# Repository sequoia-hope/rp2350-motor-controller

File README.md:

# rp2350-motor-controller

---- work in progress ----

This board is open source.

Design by Sequoia Hope Alexander. 

I want to build tools that help people get what they need. 

Follow me on Bluesky:
    https://bsky.app/profile/sequoia.farm

CERN-OHL-P license. See LICENSE file for details.

A brushless motor controller and servomotor controller for robotics.

This board is designed to be fabricated at JLCPCB by anyone. All of the
components have been sourced to be in stock in high volumes and low cost
at LCSC/JLCPCB. When the board is ready, you can order them yourself at cost
by uploading a zip file to JLCPCB for under $50 per board QTY 10.

Board features:
--
 - Dual core 150MHz RP2350B CPU with floating point and excellent firmware APIs
 - Four independent software-controlled half-h bridges
 - Supports brushless motors, stepper motors, or two brushed motors.
 - SimpleFOC firmware support
 - Maximum 60 volts on 80V silicon (FETs, buck), with TVS breakdown set just
   below the FET rating so surges hit the TVS first (SMAJ64A phases, SMDJ64A
   bus). Rev A boards are limited to ~48V by their 51V-standoff phase TVS.
   A 72V-bus variant needs six BOM changes (100V FETs, 78A-grade TVS, 100V
   buck, 4.3k divider bottoms, no LM74700) — see review/power.html.
 - Current range set by the phase shunts — see the table below
 - Phase voltage sensing for three phases
 - Phase current sensing for three phases
 - Input voltage sensing
 - Temperature sensing for both the FETS and motor.
 - Isolated CAN bus port
 - USB-C can be used for Micropython development, USB serial, or gamepad emulation for force feedback wheels or other devices.
 - Advanced 12-pin encoder port
    - Active signal switching reroutes physical I/O pins to multiple signal conditioning circuits.
    - Four bidirectional differential line drivers with common mode filters
    - Switchable filtering for single ended hall sensor support
    - Support for single ended or differential SPI or quadrature encoders
    - Dual channel analog encoder support for sin/cos or linear analog sensors
    - I2C sensor support
    - Switchable encoder output voltage - 3.3v or 5v - so nearly any sensor can easily be connected
    - Unused line drivers can be used as additional high speed bidirectional comms.
 - All configuration happens in software, no jumpers needed. 
 - Expandable emergency stop circuit

 - Phase and encoder leads on one side of the board, data connectors on the other
    - It is possible to design a PCB which mates to both the phase and encoder leads, to make connector adapter PCBs to your preferred motor and encoder PCBs.
 - Boards can be daisy-chained side to side, passing motor power and data via serial.
 
Current sensing (INA240A1D, 20x gain, mid-rail reference):
--
The measurable range is set by the phase shunt value. Keep the firmware
`SHUNT_RESISTOR` define in sync with what is populated, and keep
`current_limit` below the saturation ceiling (the firmware clamps this).

| Shunt (per phase) | V/A  | Measurable range |
|-------------------|------|------------------|
| 20 mΩ             | 0.40 | ±4.1 A           |
| 10 mΩ             | 0.20 | ±8.2 A           |
| 5 mΩ              | 0.10 | ±16.5 A          |
| 2×8 mΩ (=4 mΩ, schematic default) | 0.08 | ±20.6 A |

Encoder port, single-ended vs differential (rev B):
--
Each channel's 100Ω termination sits behind an analog switch on `TERM_SW`
(GPIO38). Firmware drives it high for differential encoders (termination in
circuit) and low for single-ended ones — with the termination open, the
10k/10k bias holds the unused receiver input at 1.65V and any 3.3V/5V
single-ended signal clears the threshold with >1.5V of margin; 10k pull-ups
on the P lines support open-collector outputs. On rev A boards (fixed
termination) single-ended signals cannot cross the receiver threshold on the
transceiver path: use the hall path (pins 11/9/7) for single-ended
quadrature, or swap the bias resistors R86–R93 to 560Ω for push-pull
single-ended signals. GPIO38 reaches test point TP20 on rev A for bodges.
Additionally:
 ---
 - No special programmer is required, no bootloader needs to be flashed.
 - Supports the Raspberry Pi debugger board, or use the compatible custom debugger board which can be fabbed at JLCPCB as well.
    - https://github.com/sequoia-hope/rp2040-motor-controller/tree/main/debugger
 - PlatformIO and VSCode support with step debugging, breakpoints, memory and register views.

-------

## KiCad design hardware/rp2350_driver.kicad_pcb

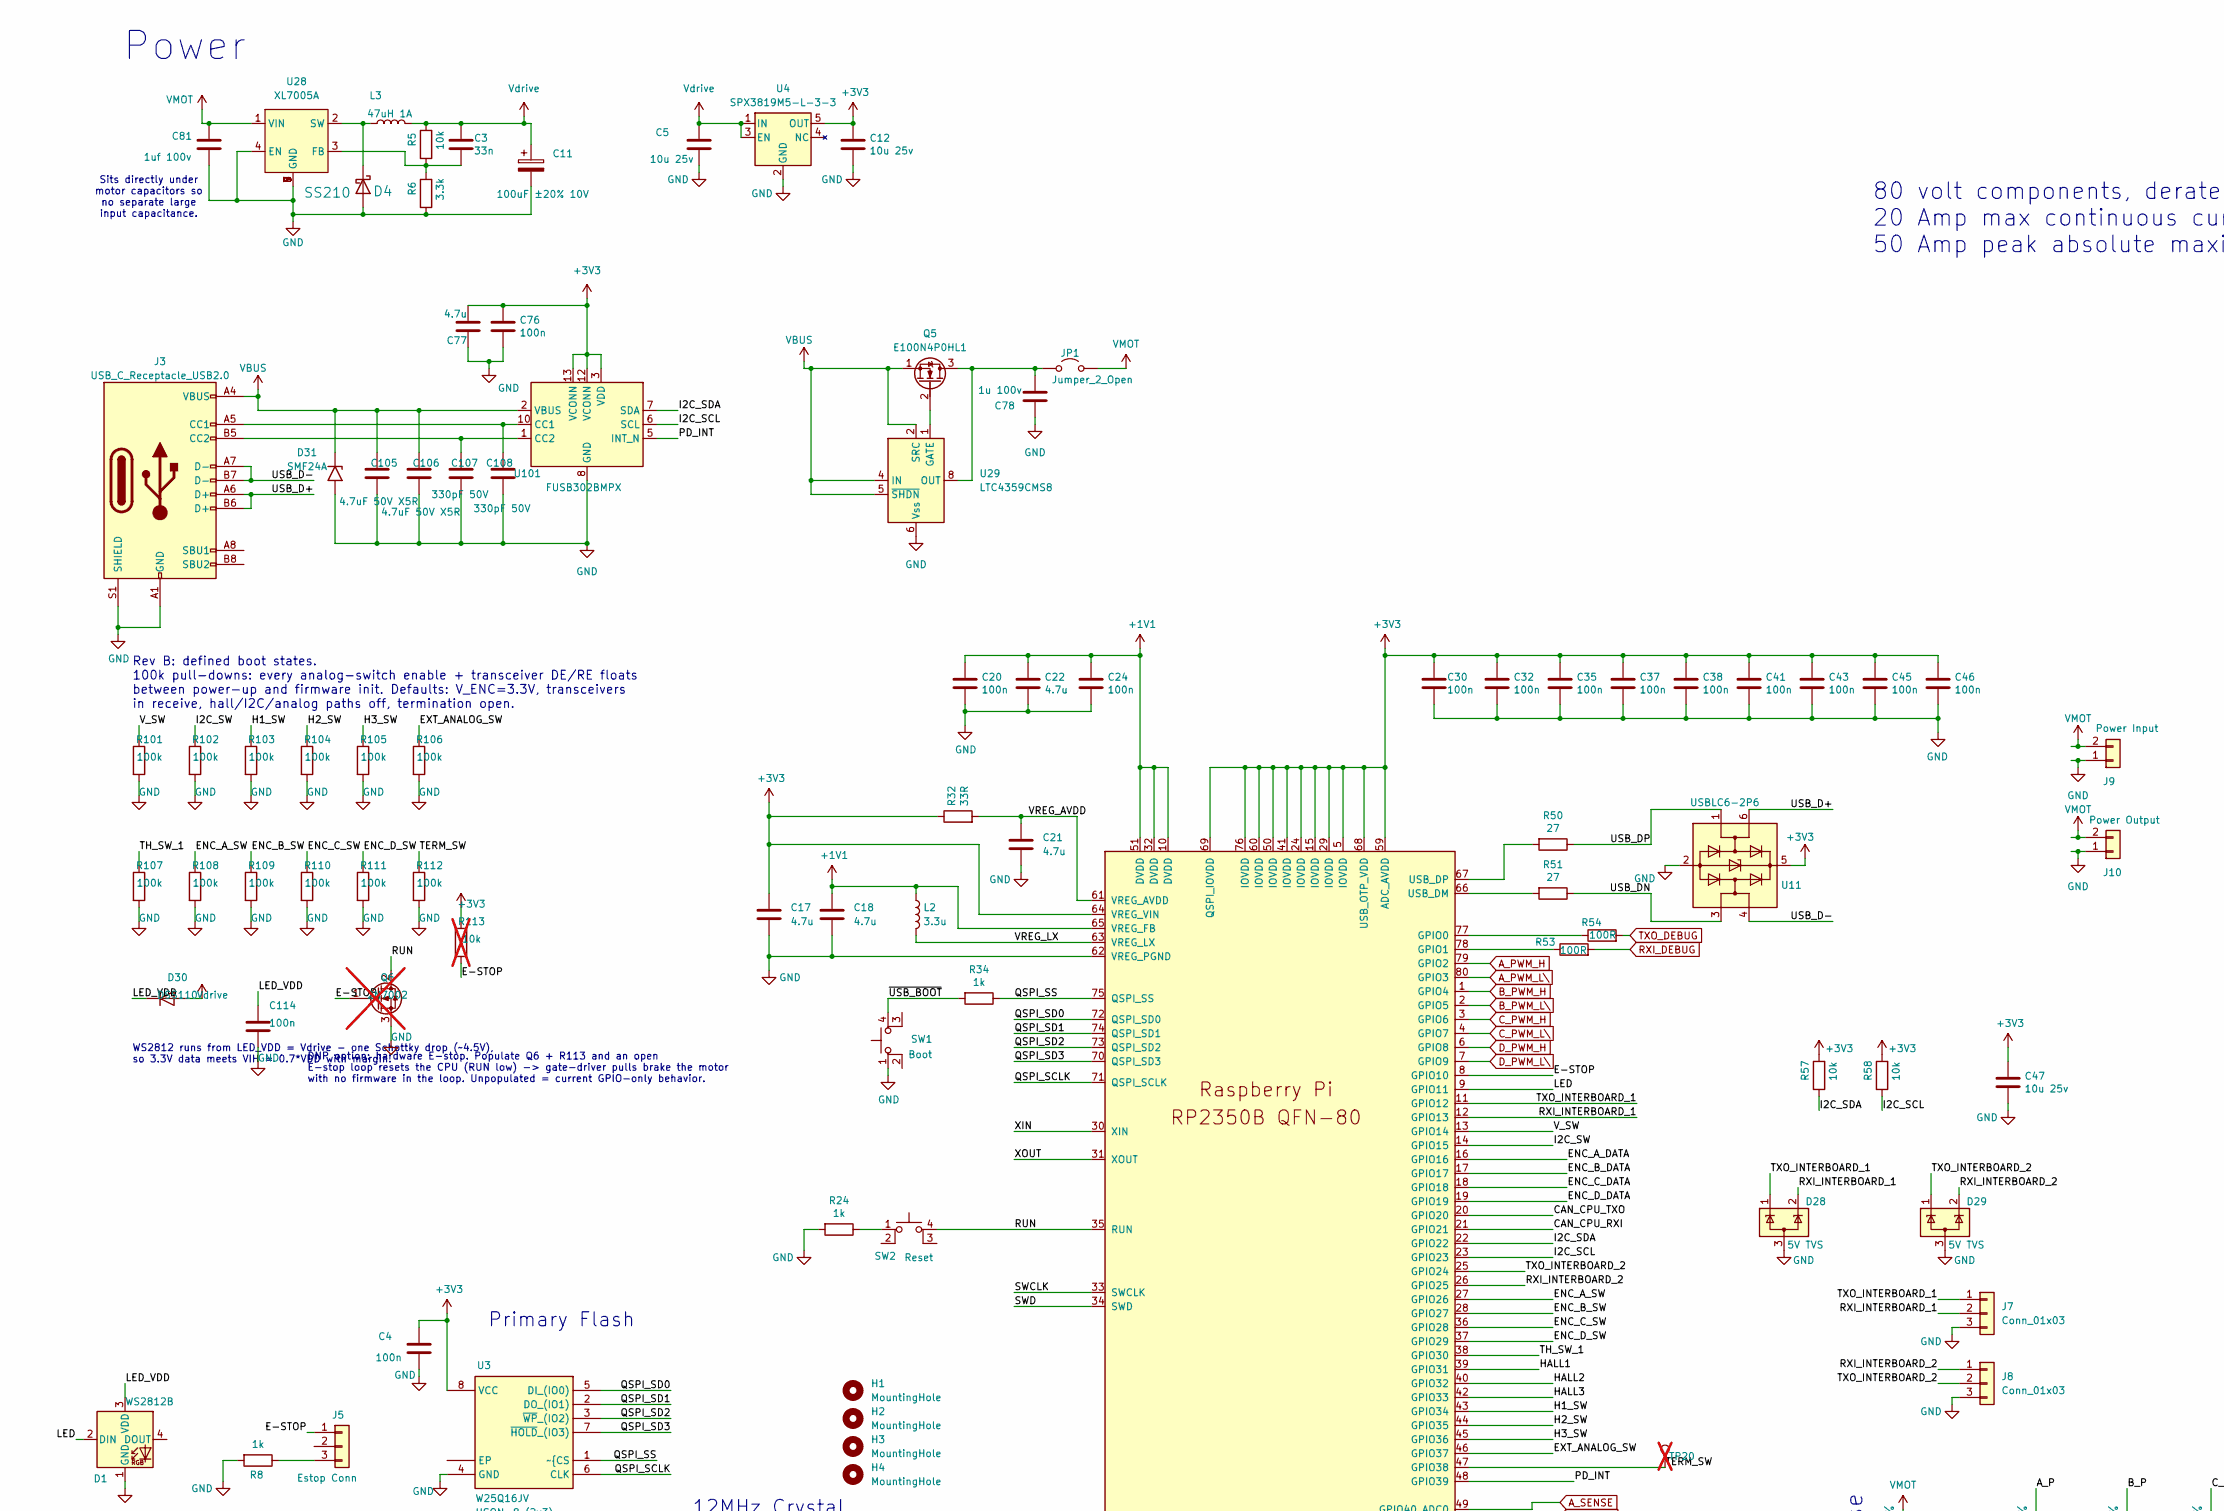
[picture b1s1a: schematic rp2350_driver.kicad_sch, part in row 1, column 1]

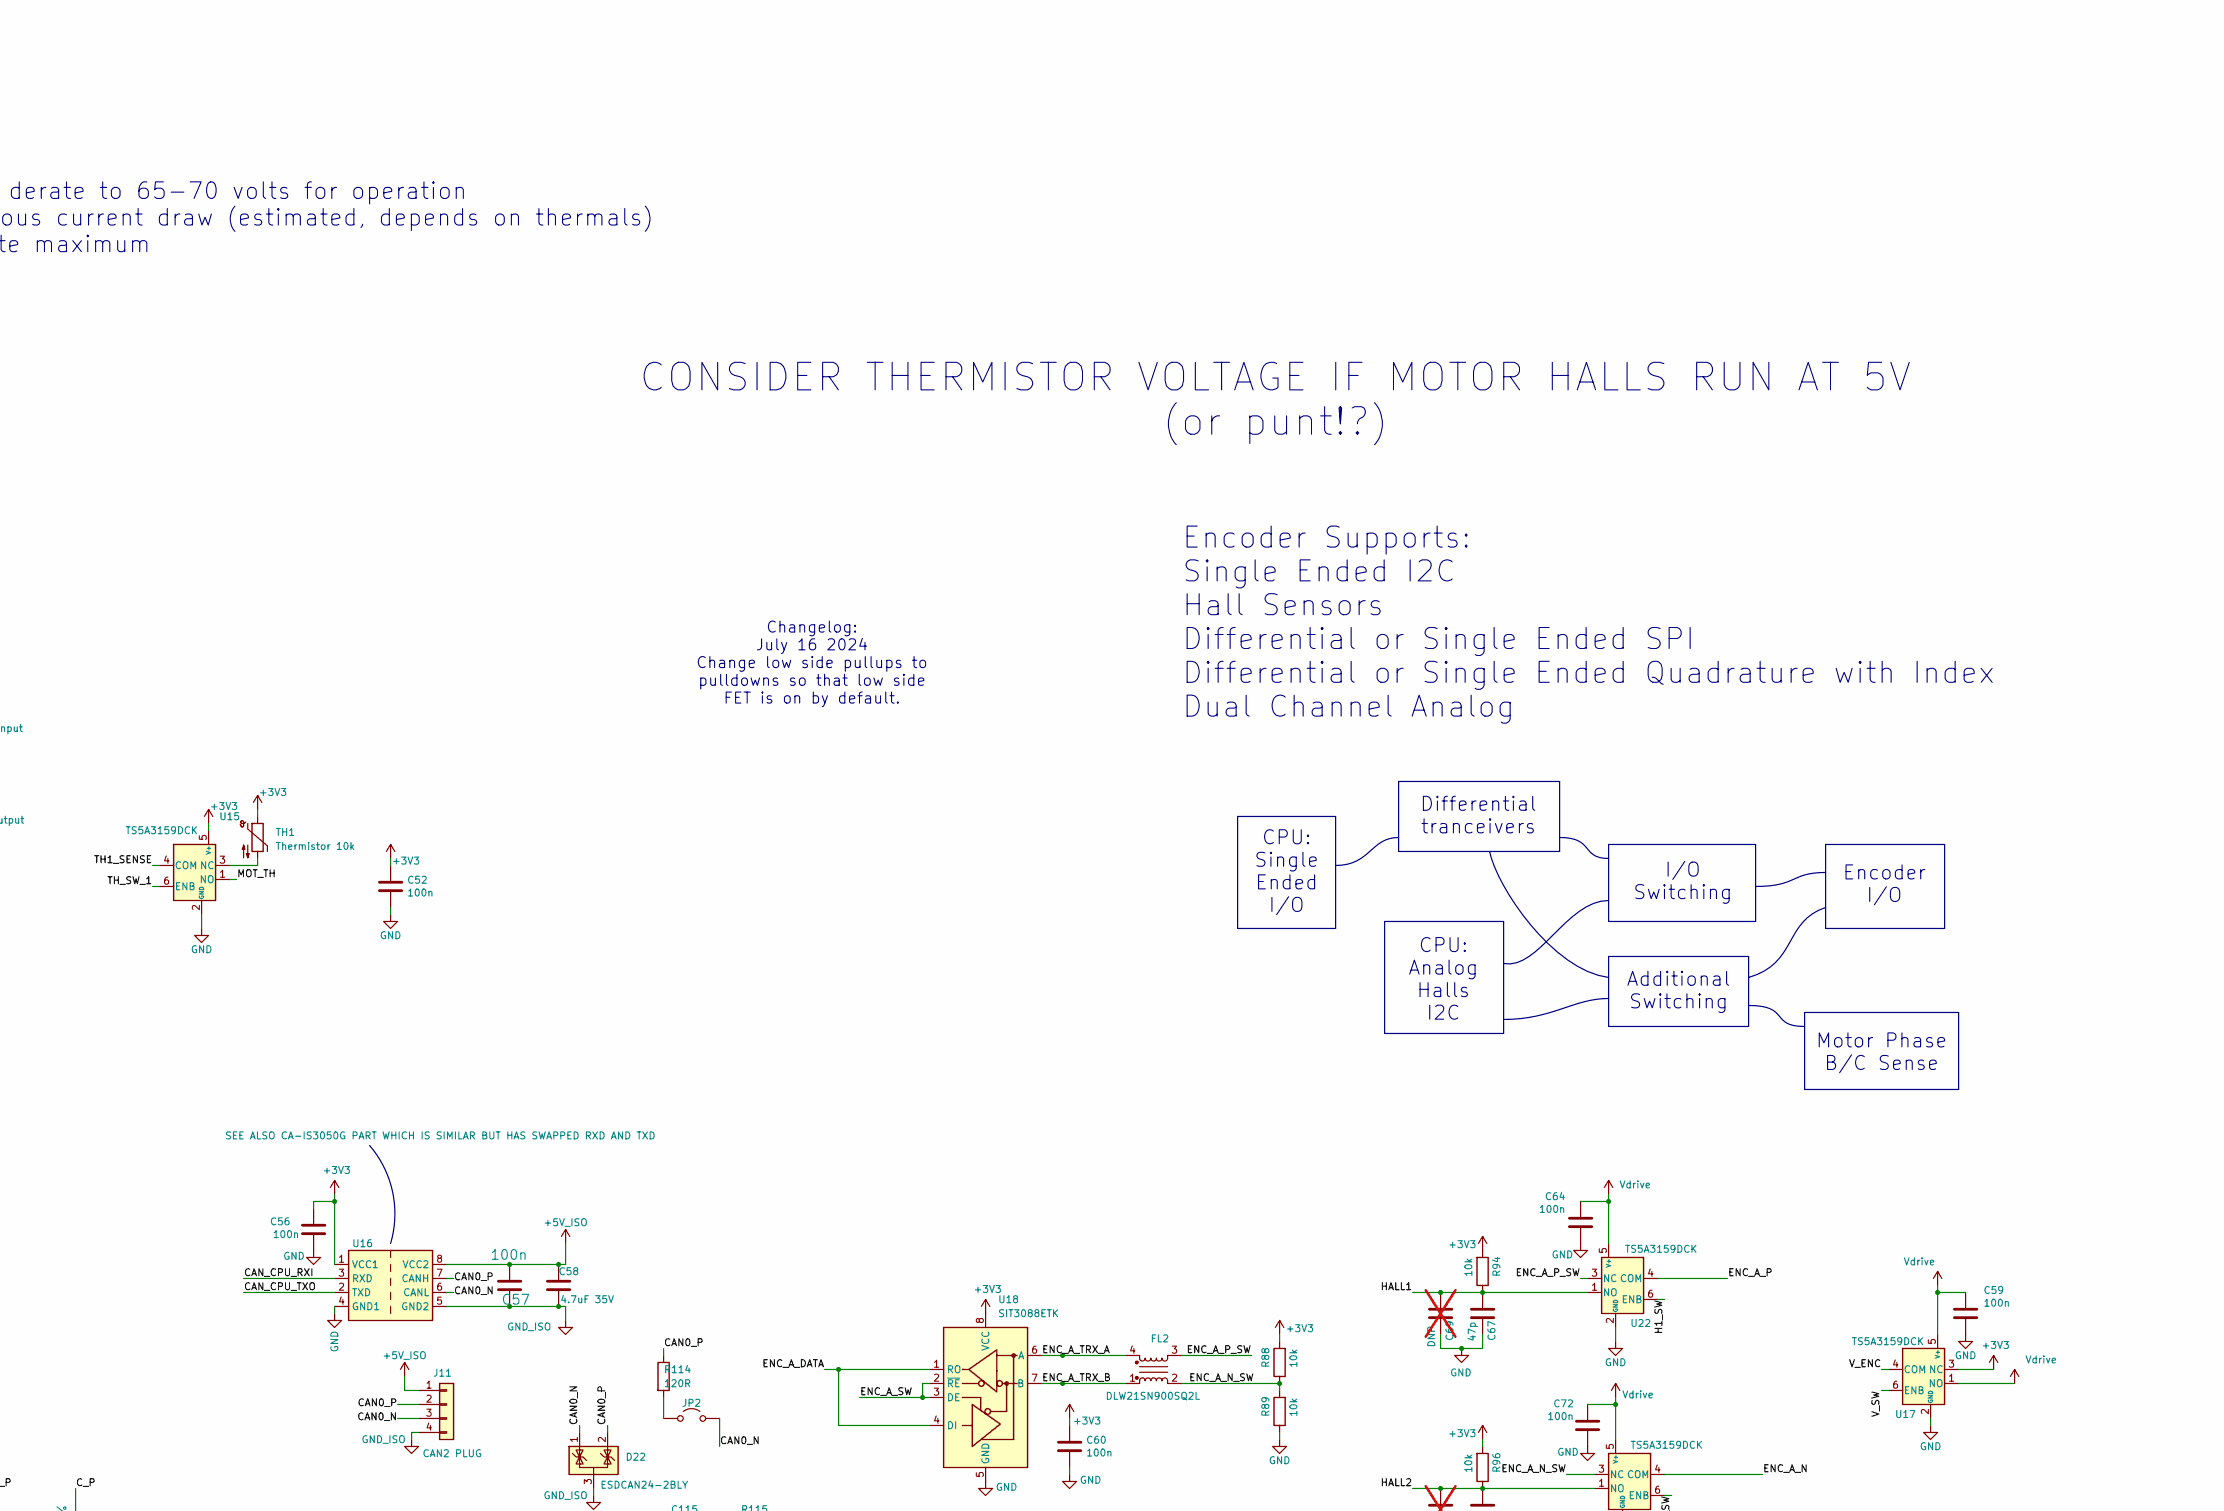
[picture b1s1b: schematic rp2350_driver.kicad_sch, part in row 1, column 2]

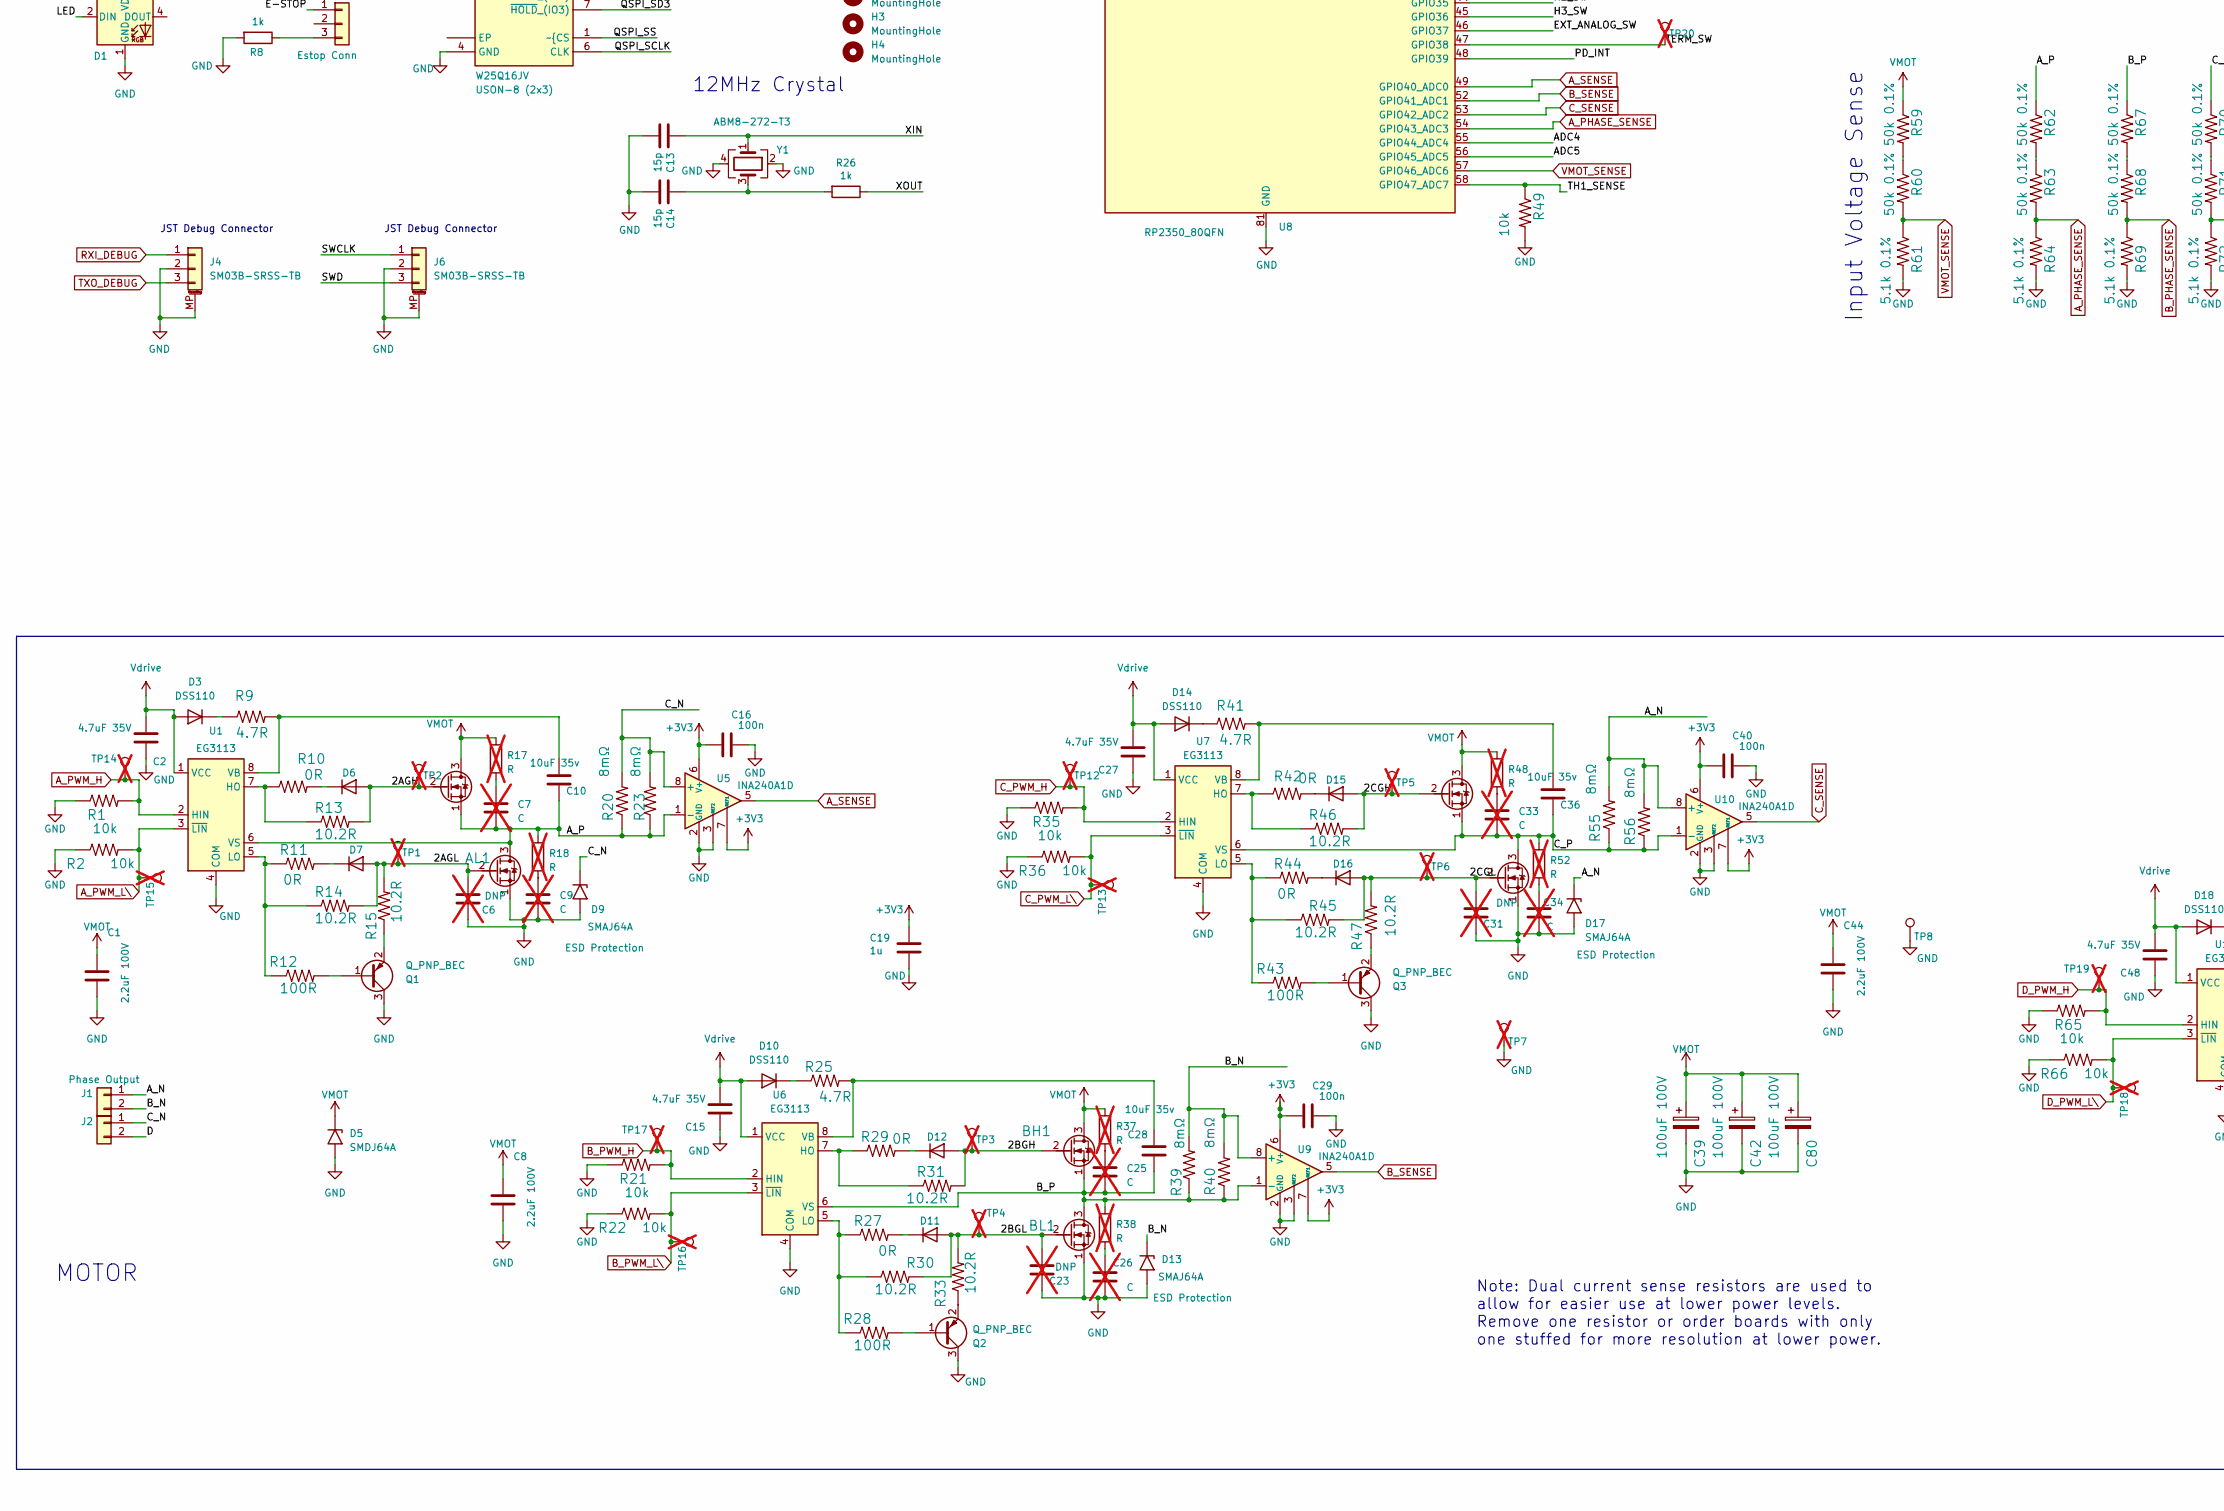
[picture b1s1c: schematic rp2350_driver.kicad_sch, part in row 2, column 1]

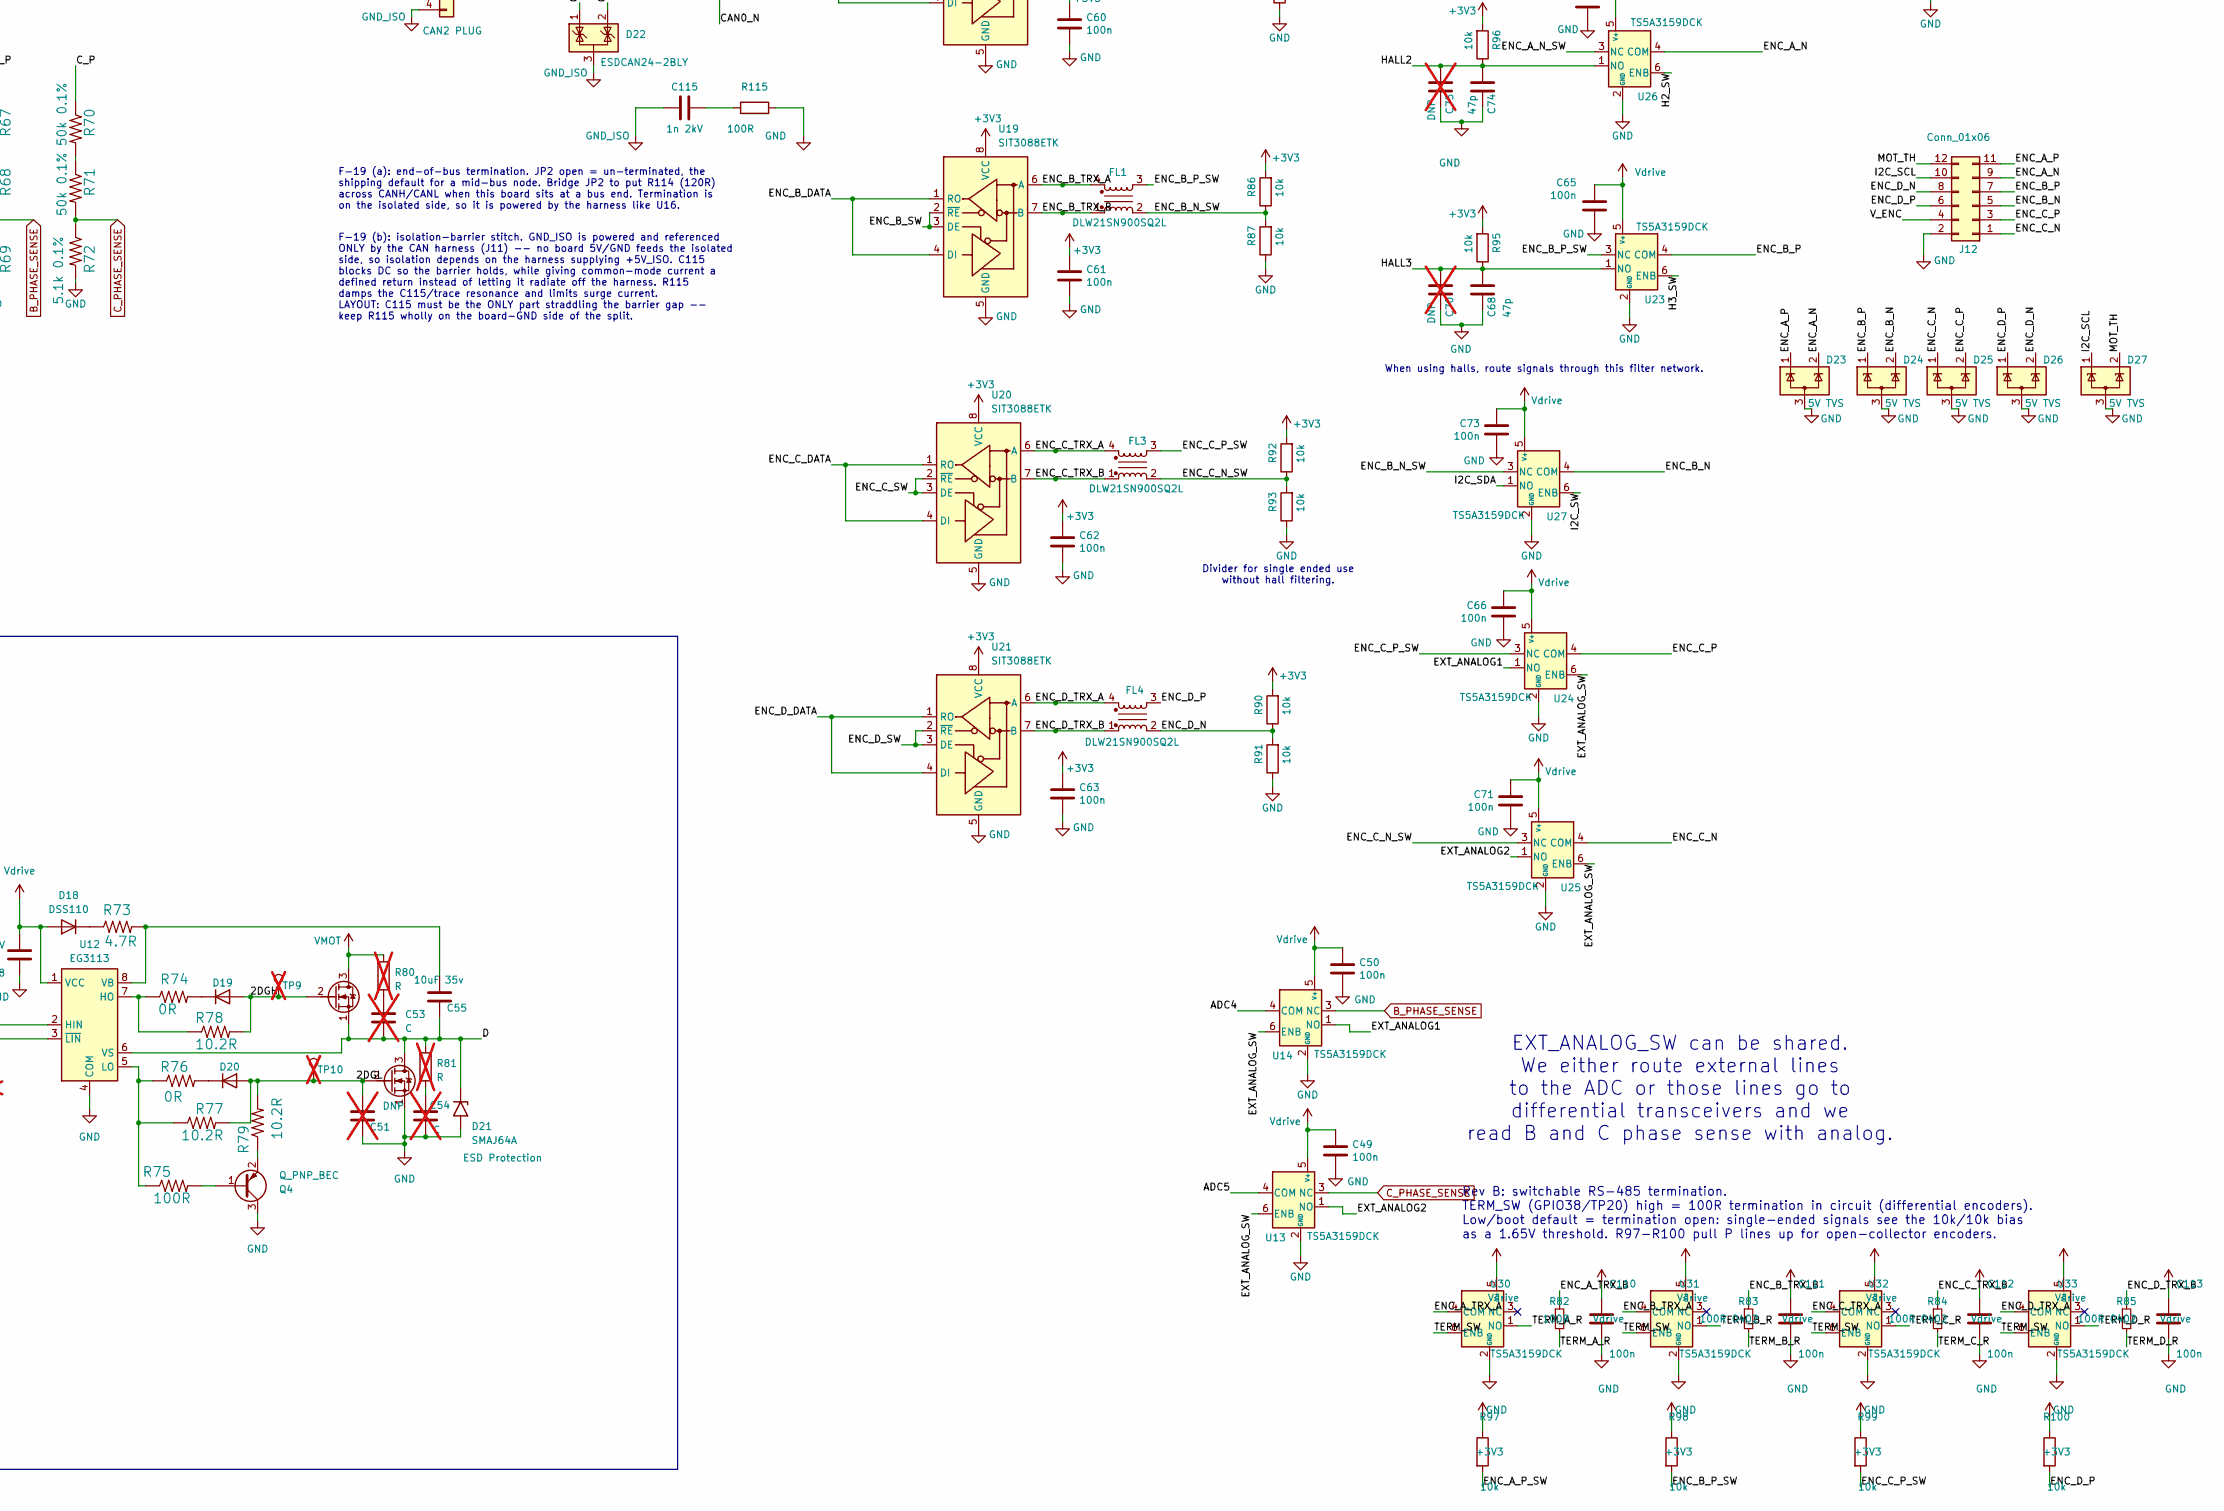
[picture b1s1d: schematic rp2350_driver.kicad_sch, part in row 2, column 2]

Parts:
AH1: BSC030N08NS5; PowerPAK_SO-8_123; LCSC C501507
AL1: BSC030N08NS5; PowerPAK_SO-8_123; LCSC C501507
BH1: BSC030N08NS5; PowerPAK_SO-8_123; LCSC C501507
BL1: BSC030N08NS5; PowerPAK_SO-8_123; LCSC C501507
C1, C8, C44: 2.2uF 100V; C_1206_3216Metric; LCSC C650969
C2, C15, C27, C48: 4.7uF 35V; C_0603_1608Metric_JLC; LCSC C329940
C3: 33n; C_0402_1005Metric_JLC; LCSC C106862
C4, C20, C24, C30, C32, C35, C37, C38, C41, C43, C45, C46, C49, C50, C52, C59, C60, C61, C62, C63, C64, C65, C66, C71, C72, C73, C76, C110, C111, C112, C113, C114: 100n; C_0402_1005Metric_JLC; LCSC C131394
C5, C12, C47: 10u 25v; C_0805_2012Metric_JLC; LCSC C15850
C6, C23, C31, C51: DNP; C_0603_1608Metric_JLC; not fitted
C7, C9, C25, C26, C33, C34, C53, C54: C; C_0402_1005Metric_JLC; not fitted
C10, C28, C36, C55: 10uF 35v; C_0603_1608Metric_JLC; LCSC C194427
C11: 100uF ±20% 10V; CP_Elec_5x5.4; LCSC C191859
C13, C14: 15p; C_0402_1005Metric_JLC; LCSC C106997
C16, C29, C40, C56: 100n; C_0402_1005Metric_JLC; LCSC C14663
C17, C18: 4.7u; C_0402_1005Metric_small_pads; LCSC C368809
C19: 1u; C_0402_1005Metric_JLC; LCSC C15849
C21, C22, C77: 4.7u; C_0402_1005Metric_JLC; LCSC C368809
C39: 100uF 100V; CP_Radial_D10.0mm_P5.00mm; MPN 1011001013R00; LCSC C2887236
C42, C80: 100uF 100V; CP_Radial_D10.0mm_P5.00mm; MPN 2210631013R00; LCSC C2887236
C57: 100n; C_0603_1608Metric_JLC
C58: 4.7uF 35V; C_0603_1608Metric_JLC; Voltage 35V; LCSC C329940
C67, C68, C74: 47p; C_0402_1005Metric_JLC; LCSC C20069324
C69, C70, C75: DNP; C_0603_1608Metric_JLC; LCSC C1671; not fitted
C78: 1u 100v; C_0603_1608Metric_JLC; LCSC C23829972
C81: 1uf 100v; C_0603_1608Metric_JLC; LCSC C23829972
C105, C106: 4.7uF 50V X5R; C_0805_2012Metric_JLC; LCSC C98192
C107, C108: 330pF 50V; C_0402_1005Metric_JLC; LCSC C106206
C115: 1n 2kV; C_1206_3216Metric
CH1, CH2: BSC030N08NS5; PowerPAK_SO-8_123; LCSC C501507
CL1, CL2: BSC030N08NS5; PowerPAK_SO-8_123; LCSC C501507
D1: WS2812B; LED_WS2812B-2020_PLCC4_2.0x2.0mm_MotorBuck; LCSC C2890364
D3, D10, D14, D18, D30: DSS110; D_SOD-123F; LCSC C2923942
D4: SS210; D_SMA; LCSC C14996
D5: SMDJ64A; D_SMC; LCSC LCSC-TBD-SMDJ64A
D6, D7, D11, D12, D15, D16, D19, D20: CDBU0130R-HF; D_SOD-523; LCSC C2886025
D9, D13, D17, D21: SMAJ64A; D_SMA; LCSC LCSC-TBD-SMAJ64A
D22: ESDCAN24-2BLY; SOT-23; LCSC C5158050
D23, D24, D25, D26, D27, D28, D29: 5V TVS; SOT-883; LCSC C552559
D31: SMF24A; D_SOD-123F; LCSC C169430
FL1, FL2, FL3, FL4: DLW21SN900SQ2L; FILTER-SMD_4P-L2.0-W1.2-BL_DLW21H; LCSC C97856
H1, H2, H3, H4: MountingHole; MountingHole_3.9mm_Plastite_#6
J1, J2, J9: XT30; AMASS_XT30PW-M_1x02_P2.50mm_Horizontal; LCSC C431092
J3: USB_C_Receptacle_USB2.0; USB_C_Receptacle_XKB_U262-16XN-4BVC11; LCSC C2835315
J4, J6: SM03B-SRSS-TB; JST_SH_SM03B-SRSS-TB_1x03-1MP_P1.00mm_Horizontal; LCSC C2763613
J5: Estop Conn; BOOMELE-2510-3A_1x03_P2.54mm_Vertical; LCSC C509148
J7: Conn_01x03; PinHeader_1x03_P2.54mm_Horizontal; LCSC C492411
J8: Conn_01x03; PinSocket_1x03_P2.54mm_Horizontal; LCSC C2897385
J10: Power Output; AMASS_XT30PW-F_1x02_P2.50mm_Horizontal; LCSC C2913282
J11: CAN2 PLUG; PINREX-744-81-04TW00 _1x04_P2.54mm_Vertical; LCSC C2982033
J12: Conn_01x06; CONN12_5018761240_MOL; LCSC C493440
JP1: Jumper_2_Open; SolderJumper-2_P1.3mm_Bridged_RoundedPad1.0x1.5mm
JP2: Jumper_2_Open; SolderJumper-2_P1.3mm_Open_RoundedPad1.0x1.5mm
L2: 3.3u; L_pol_2016; LCSC C42411119
L3: 47uH 1A; L_APV_ANR5045; LCSC C520357
Q1, Q2, Q3, Q4: Q_PNP_BEC; SOT-23; LCSC C686646
Q5: E100N4P0HL1; PowerPAK_SO-8_123; LCSC C29781176
Q6: 2N7002; SOT-23; LCSC LCSC-TBD-2N7002; not fitted
R1, R2, R21, R22, R35, R36, R49, R65, R66: 10k; R_0402_1005Metric_JLC; LCSC C25804
R5, R57, R58, R86, R87, R88, R89, R90, R91, R92, R93, R94, R95, R96, R97, R98, R99, R100: 10k; R_0402_1005Metric_JLC; LCSC C60490
R6: 3.3k; R_0402_1005Metric_JLC; LCSC C2909345
R8, R24, R26, R34: 1k; R_0402_1005Metric_JLC; LCSC C11702
R9, R25, R41, R73: 4.7R; R_0603_1608Metric_JLC; LCSC C2907035
R10, R11, R27, R29, R42, R44, R74, R76: 0R; R_0603_1608Metric_JLC; LCSC C21189
R12, R28, R43, R75: 100R; R_0603_1608Metric_JLC; LCSC C22775
R13, R14, R15, R30, R31, R33, R45, R46, R47, R77, R78, R79: 10.2R; R_0603_1608Metric_JLC; LCSC C2933129
R17, R18, R37, R38, R48, R52, R80, R81: R; R_0603_1608Metric_JLC; not fitted
R20, R23, R39, R40, R55, R56: 8mΩ; R_2512_6332Metric; LCSC C2904240
R32: 33R; R_0402_1005Metric_JLC; LCSC C25105
R50, R51: 27; R_0402_1005Metric_JLC; LCSC C25100
R53, R54: 100R; R_0402_1005Metric_JLC; LCSC C22775
R59, R60, R62, R63, R67, R68, R70, R71: 50k 0.1%; R_0603_1608Metric_JLC; LCSC C861451
R61, R64, R69, R72: 5.1k 0.1%; R_0603_1608Metric_JLC; LCSC C122969
R82: 100R; R_0402_1005Metric_JLC; LCSC C106232
R83, R84, R85: 100R 0402; R_0402_1005Metric_JLC; LCSC C106232
R101, R102, R103, R104, R105, R106, R107, R108, R109, R110, R111, R112: 100k; R_0402_1005Metric_JLC; LCSC LCSC-TBD-100k-0402
R113: 10k; R_0402_1005Metric_JLC; LCSC C60490; not fitted
R114: 120R; R_0603_1608Metric
R115: 100R; R_0603_1608Metric
SW1, SW2: Button; KEY-SMD_4P-L4.2-W3.2-P2.20-LS4.6; LCSC C19724063
TH1: Thermistor 10k; R_0603_1608Metric_JLC; LCSC C13564
TP1, TP2, TP3, TP4, TP5, TP6, TP7, TP9, TP10: TestPoint; TestPoint_Pad_D1.5mm_no_courtyard; not fitted
TP8: TestPoint; TestPoint_Pad_D1.5mm_no_courtyard; LCSC C238130
TP12, TP13, TP14, TP15, TP16, TP17, TP18, TP19, TP20: TestPoint; TestPoint_Pad_D1.0mm_no_courtyard; not fitted
U1, U6, U7, U12: EG3113; SOIC-8_3.9x4.9mm_P1.27mm; LCSC C480666
U3: W25Q16JV; IC_W25Q16JVUXIQ_TR; MPN W25Q16JVUXIQ; LCSC C2843335
U4: SPX3819M5-L-3-3; SOT-23-5; LCSC C20617301
U5, U9, U10: INA240A1D; SOIC-8_3.9x4.9mm_P1.27mm; LCSC C1346458
U8: RP2350_80QFN; RP2350-QFN-80-1EP_10x10_P0.4mm_EP3.4x3.4mm_ThermalVias; LCSC C42415655
U11: USBLC6-2P6; SOT-666; LCSC C2827693
U13, U14, U15, U17, U22, U23, U24, U25, U26, U27, U30, U31, U32, U33: TS5A3159DCK; SOT-363_SC-70-6_JLC; LCSC C46388
U16: CA-IS3052CG; SOIC-8_7.5x5.85mm_P1.27mm; LCSC C41784142
U18, U19, U20, U21: SIT3088ETK; DFN-8_L3.0-W3.0-P0.65-BL-EP; LCSC C601076
U28: XL7005A; SOIC-8-1EP_3.9x4.9mm_P1.27mm_EP2.29x3mm; LCSC C50848
U29: LTC4359CMS8; MSOP-8_3x3mm_P0.65mm; LCSC C688235
U101: FUSB302BMPX; WQFN-14-1EP_2.5x2.5mm_P0.5mm_EP1.45x1.45mm; LCSC C442699
Y1: ABM8-272-T3; Crystal_SMD_3225-4Pin_3.2x2.5mm; LCSC C20625731

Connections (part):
+1V1: C18.1, C20.1, C22.1, C24.1, L2.1, U8.10 (DVDD), U8.32 (DVDD), U8.51 (DVDD), U8.65 (VREG_FB)
+3V3: C4.1, C12.1, C16.1, C17.1, C19.1, C29.1, C30.1, C32.1, C35.1, C37.1, C38.1, C40.1, C41.1, C43.1, C45.1, C46.1, C47.1, C52.1, C56.1, C60.1, C61.1, C62.1, C63.1, C76.1, C77.1, R32.1, R57.2, R58.2, R86.2, R88.2, R90.2, R92.2, R94.2, R95.2, R96.2, R97.1, R98.1, R99.1, R100.1, R113.1, TH1.1, U3.8 (VCC), U4.5 (OUT), U5.6 (V+), U5.7 (REF1), U8.5 (IOVDD), U8.15 (IOVDD), U8.24 (IOVDD), U8.29 (IOVDD), U8.41 (IOVDD), U8.50 (IOVDD), U8.59 (ADC_AVDD), U8.60 (IOVDD), U8.64 (VREG_VIN), U8.68 (USB_OTP_VDD), U8.69 (QSPI_IOVDD), U8.76 (IOVDD), U9.6 (V+), U9.7 (REF1), U10.6 (V+), U10.7 (REF1), U11.5 (VBUS), U15.5 (V+), U16.1 (VCC1), U17.3 (NC), U18.8 (VCC), U19.8 (VCC), U20.8 (VCC), U21.8 (VCC), U101.3 (VDD), U101.4 (VDD), U101.12 (VCONN), U101.13 (VCONN)
+5V_ISO: C57.2, C58.2, J11.1, U16.8 (VCC2)
/2AGH: AH1.2 (G), D6.2 (A), R13.2, TP2.1
/2AGL: AL1.2 (G), C6.2, D7.2 (A), R14.2, R15.2, TP1.1
/2BGH: BH1.2 (G), D12.2 (A), R31.2, TP3.1
/2BGL: BL1.2 (G), C23.2, D11.2 (A), R30.2, R33.2, TP4.1
/2CGH: CH1.2 (G), D15.2 (A), R46.2, TP5.1
/2CGL: C31.2, CL1.2 (G), D16.2 (A), R45.2, R47.2, TP6.1
/2DGH: CH2.2 (G), D19.2 (A), R78.2, TP9.1
/2DGL: C51.2, CL2.2 (G), D20.2 (A), R77.2, R79.2, TP10.1
/ADC4: U8.55 (GPIO44_ADC4), U14.4 (COM)
/ADC5: U8.56 (GPIO45_ADC5), U13.4 (COM)
/A_N: D17.1 (A1), J1.1, R55.2, R56.2, U10.8 (+)
/A_P: AH1.1 (S), AL1.3 (D), C7.2, C10.1, R18.1, R20.1, R23.1, R62.1, U1.6 (VS), U5.1 (-)
/B_N: D13.1 (A1), J1.2, R39.2, R40.2, U9.8 (+)
/B_P: BH1.1 (S), BL1.3 (D), C25.2, C28.1, R38.1, R39.1, R40.1, R67.1, U6.6 (VS), U9.1 (-)
/CAN0_N: D22.1 (K), J11.3, JP2.2 (B), U16.6 (CANL)
/CAN0_P: D22.2 (K), J11.2, R114.1, U16.7 (CANH)
/CAN_CPU_RXI: U8.21 (GPIO21), U16.3 (RXD)
/CAN_CPU_TXO: U8.20 (GPIO20), U16.2 (TXD)
/C_N: D9.1 (A1), J2.1, R20.2, R23.2, U5.8 (+)
/C_P: C33.2, C36.1, CH1.1 (S), CL1.3 (D), R52.1, R55.1, R56.1, R70.1, U7.6 (VS), U10.1 (-)
/D: C53.2, C55.1, CH2.1 (S), CL2.3 (D), D21.1 (A1), J2.2, R81.1, U12.6 (VS)
/E-STOP: J5.1, Q6.1 (G), R113.2, U8.8 (GPIO10)
/ENC_A_DATA: U8.16 (GPIO16), U18.1 (RO), U18.4 (DI)
/ENC_A_N: D23.2 (K), J12.9, U26.4 (COM)
/ENC_A_N_SW: FL2.2, R88.1, R89.2, U26.3 (NC)
/ENC_A_P: D23.1 (K), J12.11, U22.4 (COM)
/ENC_A_P_SW: FL2.3, R97.2, U22.3 (NC)
/ENC_A_SW: R108.1, U8.27 (GPIO26), U18.2 (~RE), U18.3 (DE)
/ENC_A_TRX_A: FL2.4, U18.6 (A), U30.4 (COM)
/ENC_A_TRX_B: FL2.1, R82.1, U18.7 (B)
/ENC_B_DATA: U8.17 (GPIO17), U19.1 (RO), U19.4 (DI)
/ENC_B_N: D24.2 (K), J12.5, U27.4 (COM)
/ENC_B_N_SW: FL1.2, R86.1, R87.2, U27.3 (NC)
/ENC_B_P: D24.1 (K), J12.7, U23.4 (COM)
/ENC_B_P_SW: FL1.3, R98.2, U23.3 (NC)
/ENC_B_SW: R109.1, U8.28 (GPIO27), U19.2 (~RE), U19.3 (DE)
/ENC_B_TRX_A: FL1.4, U19.6 (A), U31.4 (COM)
/ENC_B_TRX_B: FL1.1, R83.1, U19.7 (B)
/ENC_C_DATA: U8.18 (GPIO18), U20.1 (RO), U20.4 (DI)
/ENC_C_N: D25.1 (K), J12.1, U25.4 (COM)
/ENC_C_N_SW: FL3.2, R92.1, R93.2, U25.3 (NC)
/ENC_C_P: D25.2 (K), J12.3, U24.4 (COM)
/ENC_C_P_SW: FL3.3, R99.2, U24.3 (NC)
/ENC_C_SW: R110.1, U8.36 (GPIO28), U20.2 (~RE), U20.3 (DE)
/ENC_C_TRX_A: FL3.4, U20.6 (A), U32.4 (COM)
/ENC_C_TRX_B: FL3.1, R84.1, U20.7 (B)
/ENC_D_DATA: U8.19 (GPIO19), U21.1 (RO), U21.4 (DI)
/ENC_D_N: D26.2 (K), FL4.2, J12.8, R90.1, R91.2
/ENC_D_P: D26.1 (K), FL4.3, J12.6, R100.2
/ENC_D_SW: R111.1, U8.37 (GPIO29), U21.2 (~RE), U21.3 (DE)
/ENC_D_TRX_A: FL4.4, U21.6 (A), U33.4 (COM)
/ENC_D_TRX_B: FL4.1, R85.1, U21.7 (B)
/EXT_ANALOG1: U14.1 (NO), U24.1 (NO)
/EXT_ANALOG2: U13.1 (NO), U25.1 (NO)
/EXT_ANALOG_SW: R106.1, U8.46 (GPIO37), U13.6 (ENB), U14.6 (ENB), U24.6 (ENB), U25.6 (ENB)
/H1_SW: R103.1, U8.43 (GPIO34), U22.6 (ENB)
/H2_SW: R104.1, U8.44 (GPIO35), U26.6 (ENB)
/H3_SW: R105.1, U8.45 (GPIO36), U23.6 (ENB)
/HALL1: C67.2, C69.2, R94.1, U8.39 (GPIO31), U22.1 (NO)
/HALL2: C74.2, C75.2, R96.1, U8.40 (GPIO32), U26.1 (NO)
/HALL3: C68.2, C70.2, R95.1, U8.42 (GPIO33), U23.1 (NO)
/I2C_SCL: D27.1 (K), J12.10, R58.1, U8.23 (GPIO23), U101.6 (SCL)
/I2C_SDA: R57.1, U8.22 (GPIO22), U27.1 (NO), U101.7 (SDA)
/I2C_SW: R102.1, U8.14 (GPIO15), U27.6 (ENB)
/LED: D1.2 (DIN), U8.9 (GPIO11)
/LED_VDD: C114.1, D1.3 (VDD), D30.1 (K)
/MOT_TH: D27.2 (K), J12.12, U15.1 (NO)
/PD_INT: U8.48 (GPIO39), U101.5 (INT_N)
/QSPI_SCLK: U3.6 (CLK), U8.71 (QSPI_SCLK)
/QSPI_SD0: U3.5 (DI_(IO0)), U8.72 (QSPI_SD0)
/QSPI_SD1: U3.2 (DO_(IO1)), U8.74 (QSPI_SD1)
/QSPI_SD2: U3.3 (~WP_(IO2)), U8.73 (QSPI_SD2)
/QSPI_SD3: U3.7 (~HOLD_(IO3)), U8.70 (QSPI_SD3)
/QSPI_SS: R34.1, U3.1 (~{CS), U8.75 (QSPI_SS)
/RUN: Q6.2 (D), SW2.4 (A), U8.35 (RUN)
/RXI_INTERBOARD_1: D28.2 (K), J7.2, U8.12 (GPIO13)
/RXI_INTERBOARD_2: D29.2 (K), J8.1, U8.26 (GPIO25)
/SWCLK: J6.1, U8.33 (SWCLK)
/SWD: J6.3, U8.34 (SWD)
/TERM_A_R: R82.2, U30.1 (NO)
/TERM_B_R: R83.2, U31.1 (NO)
/TERM_C_R: R84.2, U32.1 (NO)
/TERM_D_R: R85.2, U33.1 (NO)
/TERM_SW: R112.1, TP20.1, U8.47 (GPIO38), U30.6 (ENB), U31.6 (ENB), U32.6 (ENB), U33.6 (ENB)
/TH1_SENSE: R49.1, U8.58 (GPIO47_ADC7), U15.4 (COM)
/TH_SW_1: R107.1, U8.38 (GPIO30), U15.6 (ENB)
/TXO_INTERBOARD_1: D28.1 (K), J7.1, U8.11 (GPIO12)
/TXO_INTERBOARD_2: D29.1 (K), J8.2, U8.25 (GPIO24)
/USB_D+: J3.A6 (D+), J3.B6 (D+), U11.6 (I/O1)
/USB_D-: J3.A7 (D-), J3.B7 (D-), U11.4 (I/O2)
/USB_DN: R51.1, U11.3 (I/O2)
/USB_DP: R50.1, U11.1 (I/O1)
/VREG_AVDD: C21.1, R32.2, U8.61 (VREG_AVDD)
/VREG_LX: L2.2, U8.63 (VREG_LX)
/V_ENC: J12.4, U17.4 (COM)
/V_SW: R101.1, U8.13 (GPIO14), U17.6 (ENB)
/XIN: C13.1, U8.30 (XIN), Y1.1
/XOUT: R26.1, U8.31 (XOUT)
/~USB_BOOT: R34.2, SW1.4 (A)
A_PHASE_SENSE: R63.2, R64.1, U8.54 (GPIO43_ADC3)
A_PWM_H: R1.2, TP14.1, U1.2 (HIN), U8.79 (GPIO2)
A_PWM_L\: R2.2, TP15.1, U1.3 (~LIN), U8.80 (GPIO3)
A_SENSE: U5.5, U8.49 (GPIO40_ADC0)
B_PHASE_SENSE: R68.2, R69.1, U14.3 (NC)
B_PWM_H: R21.2, TP17.1, U6.2 (HIN), U8.1 (GPIO4)
B_PWM_L\: R22.2, TP16.1, U6.3 (~LIN), U8.2 (GPIO5)
B_SENSE: U8.52 (GPIO41_ADC1), U9.5
C_PHASE_SENSE: R71.2, R72.1, U13.3 (NC)
C_PWM_H: R35.2, TP12.1, U7.2 (HIN), U8.3 (GPIO6)
C_PWM_L\: R36.2, TP13.1, U7.3 (~LIN), U8.4 (GPIO7)
C_SENSE: U8.53 (GPIO42_ADC2), U10.5
D_PWM_H: R65.2, TP19.1, U8.6 (GPIO8), U12.2 (HIN)
D_PWM_L\: R66.2, TP18.1, U8.7 (GPIO9), U12.3 (~LIN)
GND: AL1.1 (S), BL1.1 (S), C1.2, C2.1, C4.2, C5.2, C6.1, C8.2, C9.2, C11.2, C12.2, C13.2, C14.2, C15.1, C16.2, C17.2, C18.2, C19.2, C20.2, C21.2, C22.2, C23.1, C24.2, C26.2, C27.1, C29.2, C30.2, C31.1, C32.2, C34.2, C35.2, C37.2, C38.2, C39.2, C40.2, C41.2, C42.2, C43.2, C44.2, C45.2, C46.2, C47.2, C48.1, C49.2, C50.2, C51.1, C52.2, C54.2, C56.2, C59.2, C60.2, C61.2, C62.2, C63.2, C64.2, C65.2, C66.2, C67.1, C68.1, C69.1, C70.1, C71.2, C72.2, C73.2, C74.1, C75.1, C76.2, C77.2, C78.1, C80.2, C81.2, C105.2, C106.2, C107.1, C108.1, C110.2, C111.2, C112.2, C113.2, C114.2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
GND_ISO: C57.1, C58.1, C115.1, D22.3 (A), J11.4, U16.5 (GND2)
unnamed: C7.1, R17.2
unnamed: C9.1, R18.2
unnamed: C14.1, R26.2, Y1.3
unnamed: C25.1, R37.2
unnamed: C26.1, R38.2
unnamed: C33.1, R48.2
unnamed: C34.1, R52.2
unnamed: C53.1, R80.2
unnamed: C54.1, R81.2
unnamed: C115.2, R115.1
unnamed: D3.1 (K), R9.1
unnamed: D4.1 (K), L3.1, U28.2 (SW)
unnamed: D6.1 (K), R10.2
unnamed: D7.1 (K), R11.2
unnamed: D10.1 (K), R25.1
unnamed: D11.1 (K), R27.2
unnamed: D12.1 (K), R29.2
unnamed: D14.1 (K), R41.1
unnamed: D15.1 (K), R42.2
unnamed: D16.1 (K), R44.2
unnamed: D18.1 (K), R73.1
unnamed: D19.1 (K), R74.2
unnamed: D20.1 (K), R76.2
unnamed: C108.2, J3.A5 (CC1), U101.10 (CC1), U101.11 (CC1)
unnamed: C107.2, J3.B5 (CC2), U101.1 (CC2), U101.14 (CC2)
unnamed: J5.3, R8.1
unnamed: C78.2, JP1.1 (A), Q5.3 (D), U29.8 (OUT)
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
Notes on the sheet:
I/O Switching
JST Debug Connector
Primary Flash
MOTOR
CONSIDER THERMISTOR VOLTAGE IF MOTOR HALLS RUN AT 5V (or punt!?)
Differential tranceivers
Power
CPU: Single Ended I/O
12MHz Crystal
Encoder I/O
CPU: Analog Halls I2C
Sits directly under motor capacitors so no separate large input capacitance.
80 volt components, derate to 65-70 volts for operation 20 Amp max continuous current draw (estimated, depends on thermals) 50 Amp peak absolute maximum
Changelog: July 16 2024 Change low side pullups to pulldowns so that low side FET is on by default.
Note: Dual current sense resistors are used to allow for easier use at lower power levels. Remove one resistor or order boards with only one stuffed for more resolution at lower power.
Divider for single ended use without hall filtering.
EXT_ANALOG_SW can be shared. We either route external lines to the ADC or those lines go to differential transceivers and we read B and C phase sense with analog.
Encoder Supports: Single Ended I2C Hall Sensors Differential or Single Ended SPI Differential or Single Ended Quadrature with Index Dual Channel Analog
Additional Switching
Input Voltage Sense
When using halls, route signals through this filter network.
Motor Phase B/C Sense
Rev B: switchable RS-485 termination. TERM_SW (GPIO38/TP20) high = 100R termination in circuit (differential encoders). Low/boot default = termination open: single-ended signals see the 10k/10k bias as a 1.65V threshold. R97-R100 pull P lines up for open-collector encoders.
Rev B: defined boot states. 100k pull-downs: every analog-switch enable + transceiver DE/RE floats between power-up and firmware init. Defaults: V_ENC=3.3V, transceivers in receive, hall/I2C/analog paths off, termination open.
WS2812 runs from LED_VDD = Vdrive - one Schottky drop (~4.5V), so 3.3V data meets VIH = 0.7*VDD with margin.
DNP option: hardware E-stop. Populate Q6 + R113 and an open E-stop loop resets the CPU (RUN low) -> gate-driver pulls brake the motor with no firmware in the loop. Unpopulated = current GPIO-only behavior.
F-19 (a): end-of-bus termination. JP2 open = un-terminated, the shipping default for a mid-bus node. Bridge JP2 to put R114 (120R) across CANH/CANL when this board sits at a bus end. Termination is on the isolated side, so it is powered by the harness like U16.
F-19 (b): isolation-barrier stitch. GND_ISO is powered and referenced ONLY by the CAN harness (J11) -- no board 5V/GND feeds the isolated side, so isolation depends on the harness supplying +5V_ISO. C115 blocks DC so the barrier holds, while giving common-mode current a defined return instead of le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
